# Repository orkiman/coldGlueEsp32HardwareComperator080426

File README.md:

# Cold Glue Controller — Main Controller Firmware (Stage 1)

ESP32-S3-WROOM-1-N16R8 firmware for a 4-channel high-speed cold-glue gun
controller. Up to 330 Hz droplet rate; current chopping is handled by the
on-board LM339 hardware loop. The ESP32 only orchestrates phase transitions.

See `docs/initial prompt.md` for the full hardware architecture and operational
spec.

## Toolchain

PlatformIO (recommended). Open the project folder in VS Code with the
PlatformIO extension and use `PlatformIO: Upload` / `Monitor`.

```
pio run -t upload
pio device monitor
```

## Source Tree

```
src/
  main.cpp                          task wiring + boot order
  config/Config.{h,cpp}             double-buffered config + pattern storage
  comms/
    Events.{h,cpp}                  Core1->Core0 lock-free event queue
    UartJson.{h,cpp}                NDJSON parser + command dispatcher
  hw/
    Pins.h                          pin map (verbatim from docs)
    Driver.{h,cpp}                  IN1/IN2/MUX_SELECT abstraction, killAll
    Dac.{h,cpp}                     MCP4728 with task-serialized I2C writes
    Encoder.{h,cpp}                 PCNT counter + photocell ISR (any-edge)
  rt/
    GunSequencer.{h,cpp}            per-gun Peak/Hold/Decay state machine
    PatternScheduler.{h,cpp}        sheet FIFO + lazy pattern walker
    Control.{h,cpp}                 surface called by JSON dispatcher
  sys/
    Fault.{h,cpp}                   nFAULT ISR -> master kill
    Watchdog.{h,cpp}                HMI link timeout
    Status.{h,cpp}                  5 Hz status emitter
```

## Task Layout

| Core | Task        | Prio | Purpose                                |
| ---- | ----------- | ---- | -------------------------------------- |
| 0    | `uart_rx`   | 4    | NDJSON parser                          |
| 0    | `evt_emit`  | 5    | Drains event queue to Serial           |
| 0    | `wdog`      | 3    | HMI link watchdog                      |
| 0    | `status`    | 2    | 5 Hz `{"event":"status"}`              |
| 1    | `pattern`   | 7    | Encoder poll + fire pattern events     |
| 1    | `dac`       | 6    | Coalesced MCP4728 I2C writes           |
| 1    | ISRs        | IRAM | Peak (x4), photocell, nFAULT, PCNT     |

## Protocol

Newline-delimited JSON over UART0 (115200 8N1) on GPIO 43 TX / GPIO 44 RX,
routed through the on-board CP2102 USB-UART for development.

Commands and events follow `docs/initial prompt.md` Section 8 exactly.

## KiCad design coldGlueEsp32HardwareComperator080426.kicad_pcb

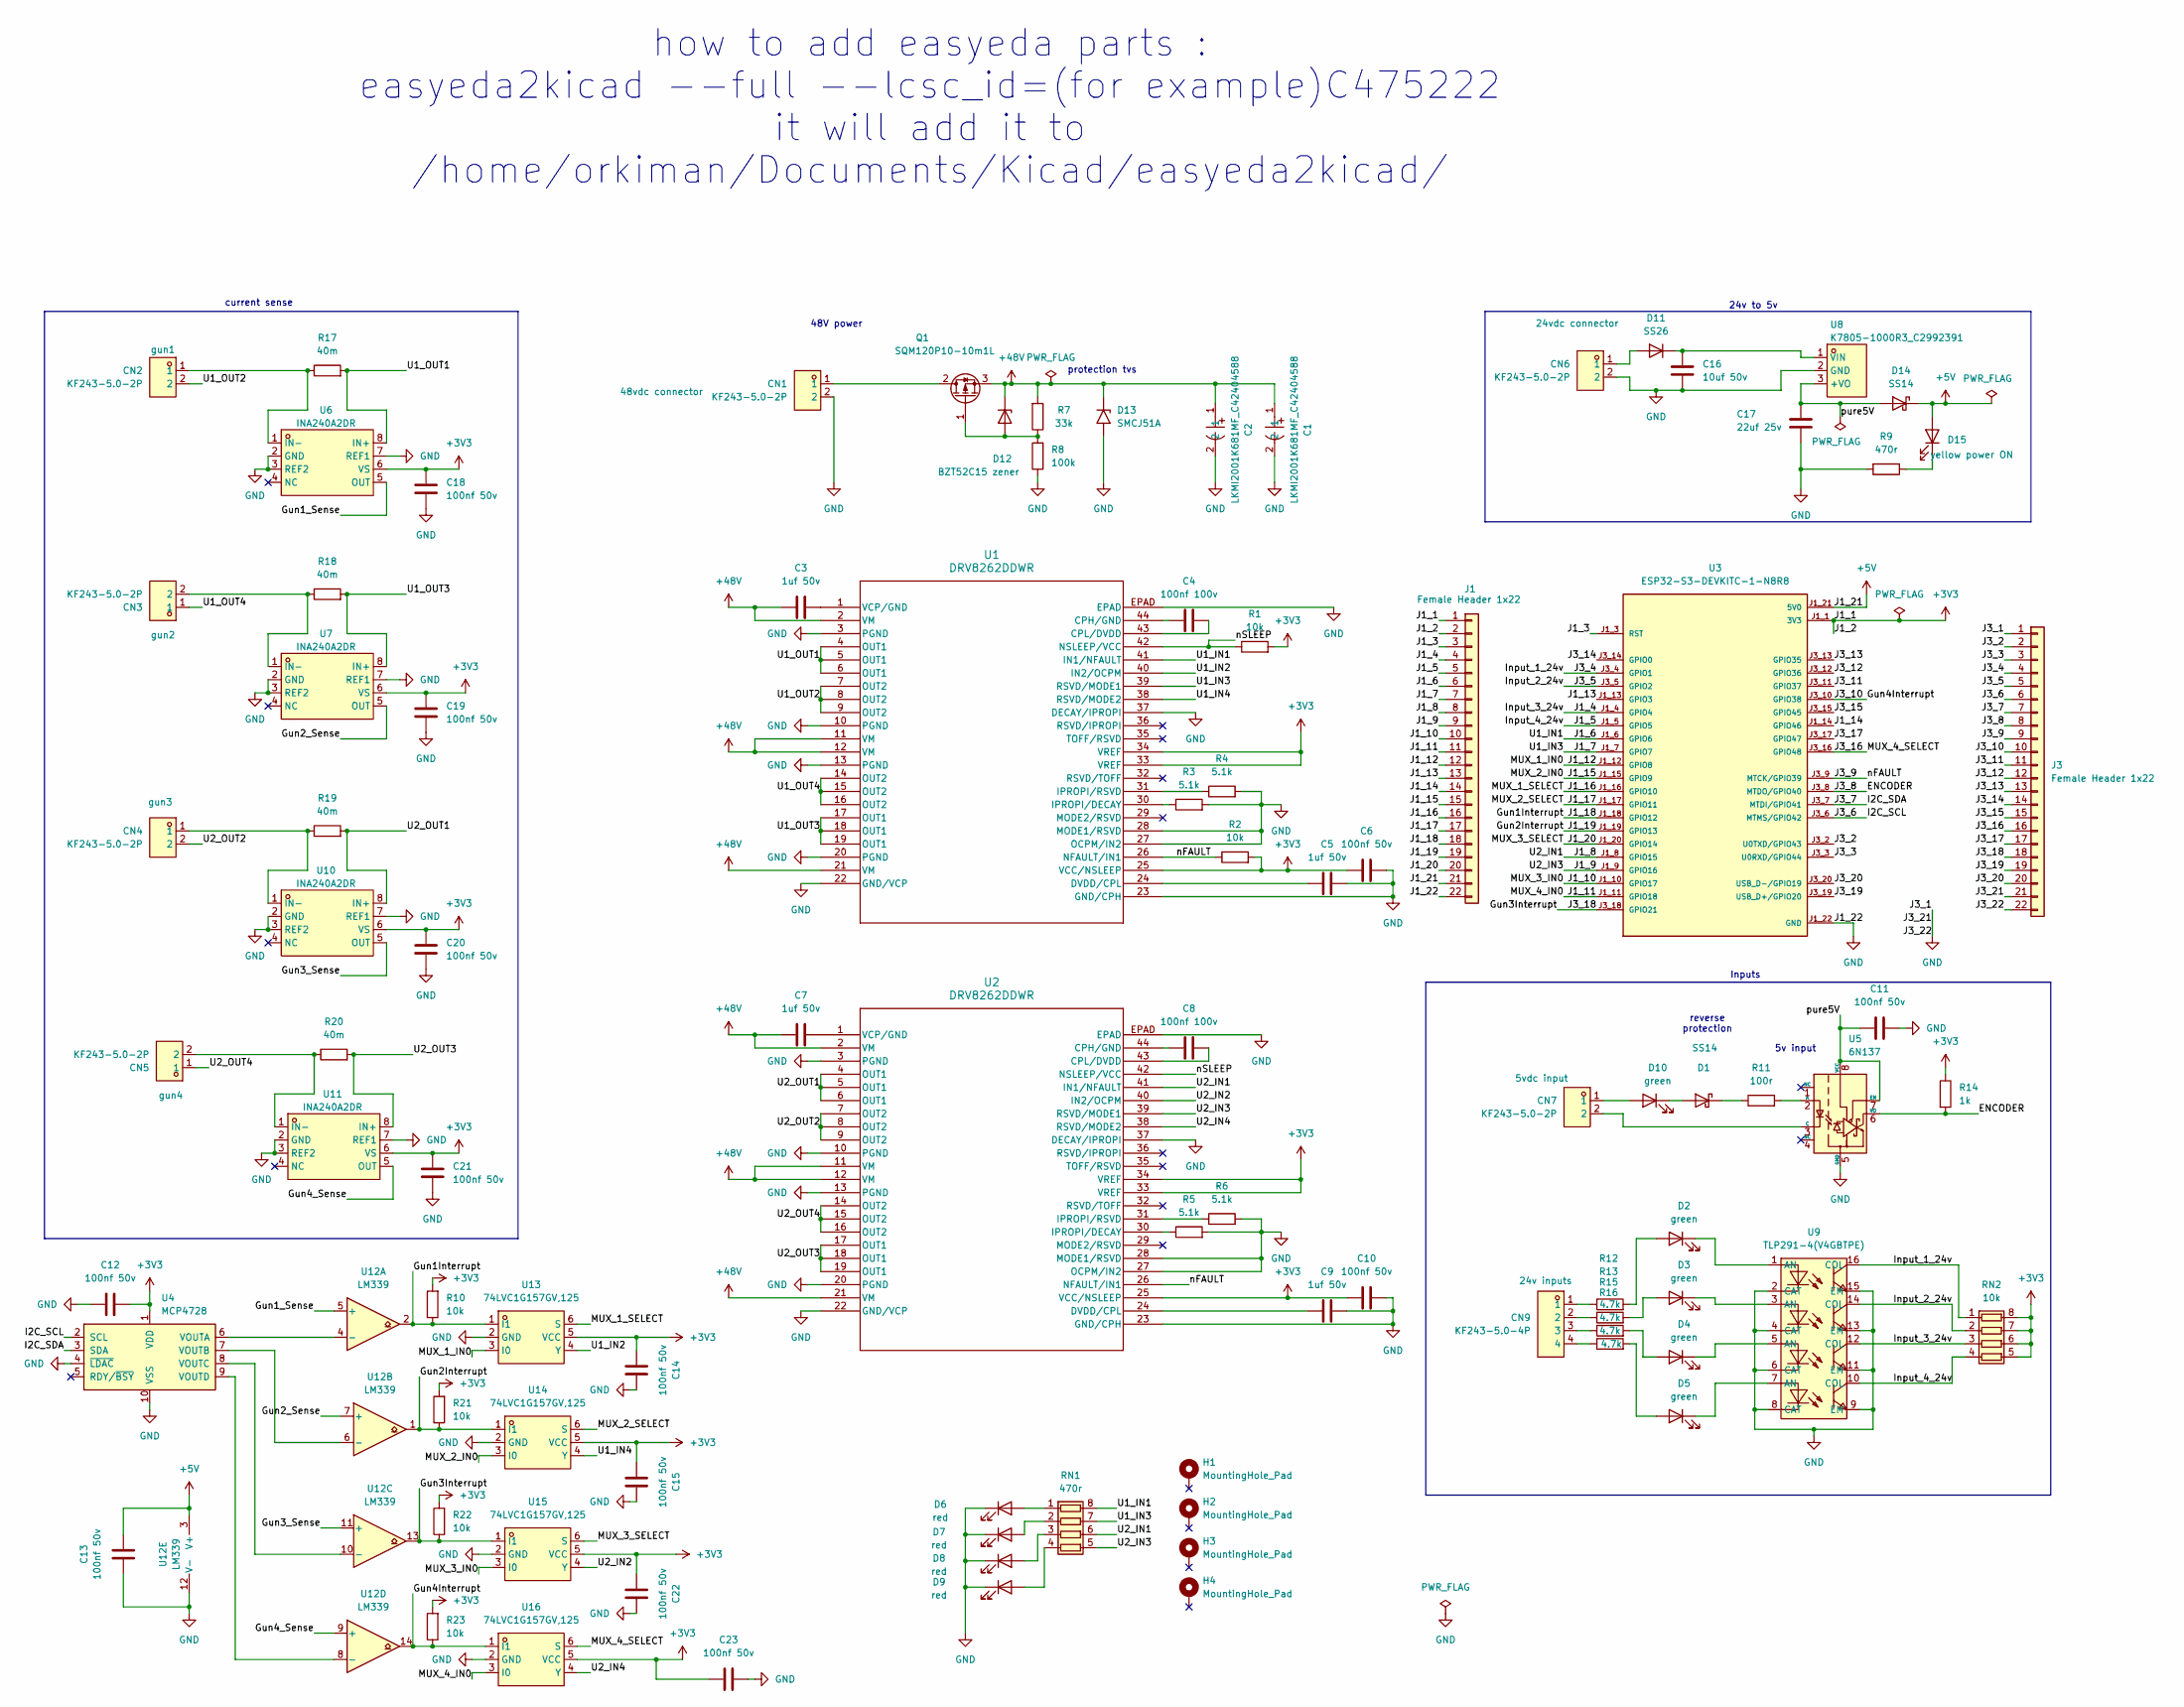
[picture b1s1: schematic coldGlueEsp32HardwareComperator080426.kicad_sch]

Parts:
C1, C2: LKMI2001K681MF_C42404588; CAP-TH_BD16.0-P7.50-D0.8-FD; LCSC part C42404588
C3, C5, C7, C9: 1uf 50v; C_0603_1608Metric; lcsc C106248
C4, C8: 100nf 100v; C_0805_2012Metric; lcsc C113803
C6, C10, C11, C12, C13, C14, C15, C22, C23: 100nf 50v; C_0603_1608Metric; lcsc C309458
C16: 10uf 50v; C_1206_3216Metric; lcsc C513774
C17: 22uf 25v; C_1206_3216Metric; lcsc C513771
C18, C19, C20, C21: 100nf 50v; C_0603_1608Metric; LCSC part C14663
CN1, CN2, CN3, CN4, CN5, CN6, CN7: KF243-5.0-2P; CONN-TH_P5.00_KF243-5.0-2P; LCSC part C475222
CN9: KF243-5.0-4P; CONN-TH_4P-P5.00_KF243-5.0-4P; LCSC part C475224
D1: SS14; D_SMA; part ss14; LCSC part C2480
D2, D3, D4, D5, D10: green; LED_0805_2012Metric; lcsc C2297
D6, D7, D8, D9: red; LED_0805_2012Metric; LCSC part C84256
D11: SS26; D_SMA; part ss26; LCSC part C14238
D12: BZT52C15 zener; D_SOD-123; LCSC part C2104
D13: SMCJ51A; D_SMC; LCSC part C438115
D14: SS14; D_SMA; LCSC part C2480
D15: yellow power ON; LED_0805_2012Metric; lcsc C2297
H1, H2, H3, H4: MountingHole_Pad; MountingHole_3.2mm_M3_Pad
J1, J3: Female Header 1x22; PinSocket_1x22_P2.54mm_Vertical; LCSC part C7499337
Q1: SQM120P10-10m1L; TO-263-2; LCSC part C3281565
R1, R2, R10, R21, R22, R23: 10k; R_0603_1608Metric; lcsc C84376
R3, R4, R5, R6: 5.1k; R_0603_1608Metric; LCSC part C23186
R7: 33k; R_0805_2012Metric; LCSC part C17633
R8: 100k; R_0805_2012Metric; LCSC part C25611
R9: 470r; R_0603_1608Metric; LCSC part C23179
R11: 100r; R_0603_1608Metric; LCSC part C22775
R12, R13, R15, R16: 4.7k; R_1206_3216Metric; LCSC part C17936
R14: 1k; R_0603_1608Metric; LCSC part C21190
R17, R18, R19, R20: 40m; R_2512_6332Metric; lcsc C500722
RN1: 470r; R_Array_Convex_4x0603; LCSC part C354986
RN2: 10k; R_Array_Convex_4x0603; LCSC part C107374
U1, U2: DRV8262DDWR; HTSSOP44-DDW_TEX; LCSC part C22427252
U3: ESP32-S3-DEVKITC-1-N8R8; XCVR_ESP32-S3-DEVKITC-1-N8R2; PARTREV V1
U4: MCP4728; MSOP-10_3x3mm_P0.5mm; LCSC part C478093
U5: 6N137; SMDIP-8_W9.53mm; LCSC part C16496
U6, U7, U10, U11: INA240A2DR; SOIC-8_L4.9-W3.9-P1.27-LS6.0-BL; LCSC part C2060768
U8: K7805-1000R3_C2992391; PWRM-TH_YLPTEC_K78XX-1000R3; LCSC part C2992391
U9: TLP291-4(V4GBTPE); SOP-16_L10.3-W4.4-P1.27-LS7.0-BL; LCSC part C2848503
U12: LM339; SOIC-14_3.9x8.7mm_P1.27mm; LCSC part C7948
U13, U14, U15, U16: 74LVC1G157GV,125; TSOP-6_L3.0-W1.5-P0.95-LS2.8-BR; MPN 74LVC1G157GV,125; LCSC part C503437

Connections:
+3V3: C6.1, C10.1, C12.2, C14.1, C15.1, C18.1, C19.1, C20.1, C21.1, C22.1, C23.1, J1.1, J1.2, R1.2, R2.2, R10.2, R14.1, R21.2, R22.2, R23.2, RN2.5 (R4.2), RN2.6 (R3.2), RN2.7 (R2.2), RN2.8 (R1.2), U1.25 (VCC/NSLEEP), U1.33 (VREF), U1.34 (VREF), U2.25 (VCC/NSLEEP), U2.33 (VREF), U2.34 (VREF), U3.J1_1 (3V3), U3.J1_2 (3V3), U4.1 (VDD), U6.6 (VS), U7.6 (VS), U10.6 (VS), U11.6 (VS), U13.5 (VCC), U14.5 (VCC), U15.5 (VCC), U16.5 (VCC)
+5V: C13.2, D14.1 (K), D15.2 (A), J1.21, U3.J1_21 (5V0), U12.3 (V+)
+48V: C1.1, C2.1, C3.1, C7.1, D12.1 (K), D13.1 (A1), Q1.3 (S), R7.2, U1.2 (VM), U1.11 (VM), U1.12 (VM), U1.21 (VM), U2.2 (VM), U2.11 (VM), U2.12 (VM), U2.21 (VM)
/ENCODER: J3.8, R14.2, U3.J3_8 (MTDO/GPIO40), U5.6 (VO)
/Gun1Interrupt: J1.18, R10.1, U3.J1_18 (GPIO12), U12.2, U13.1 (I1)
/Gun1_Sense: U6.5 (OUT), U12.5 (+)
/Gun2Interrupt: J1.19, R21.1, U3.J1_19 (GPIO13), U12.1, U14.1 (I1)
/Gun2_Sense: U7.5 (OUT), U12.7 (+)
/Gun3Interrupt: J3.18, R22.1, U3.J3_18 (GPIO21), U12.13, U15.1 (I1)
/Gun3_Sense: U10.5 (OUT), U12.11 (+)
/Gun4Interrupt: J3.10, R23.1, U3.J3_10 (GPIO38), U12.14, U16.1 (I1)
/Gun4_Sense: U11.5 (OUT), U12.9 (+)
/I2C_SCL: J3.6, U3.J3_6 (MTMS/GPIO42), U4.2 (SCL)
/I2C_SDA: J3.7, U3.J3_7 (MTDI/GPIO41), U4.3 (SDA)
/Input_1_24v: J3.4, RN2.1 (R1.1), U3.J3_4 (GPIO1), U9.16 (COL)
/Input_2_24v: J3.5, RN2.2 (R2.1), U3.J3_5 (GPIO2), U9.14 (COL)
/Input_3_24v: J1.4, RN2.3 (R3.1), U3.J1_4 (GPIO4), U9.12 (COL)
/Input_4_24v: J1.5, RN2.4 (R4.1), U3.J1_5 (GPIO5), U9.10 (COL)
/J1_3: J1.3, U3.J1_3 (RST)
/J1_6: J1.6, RN1.8 (R1.2), U1.41 (IN1/NFAULT), U3.J1_6 (GPIO6)
/J1_7: J1.7, RN1.7 (R2.2), U1.39 (RSVD/MODE1), U3.J1_7 (GPIO7)
/J1_8: J1.8, RN1.6 (R3.2), U2.41 (IN1/NFAULT), U3.J1_8 (GPIO15)
/J1_9: J1.9, RN1.5 (R4.2), U2.39 (RSVD/MODE1), U3.J1_9 (GPIO16)
/J1_10: J1.10, U3.J1_10 (GPIO17), U15.3 (I0)
/J1_11: J1.11, U3.J1_11 (GPIO18), U16.3 (I0)
/J1_12: J1.12, U3.J1_12 (GPIO8), U13.3 (I0)
/J1_13: J1.13, U3.J1_13 (GPIO3)
/J1_14: J1.14, U3.J1_14 (GPIO46)
/J1_15: J1.15, U3.J1_15 (GPIO9), U14.3 (I0)
/J1_16: J1.16, U3.J1_16 (GPIO10), U13.6 (S)
/J1_17: J1.17, U3.J1_17 (GPIO11), U14.6 (S)
/J1_20: J1.20, U3.J1_20 (GPIO14), U15.6 (S)
/J3_2: J3.2, U3.J3_2 (U0TXD/GPIO43)
/J3_3: J3.3, U3.J3_3 (U0RXD/GPIO44)
/J3_9: J3.9, R2.1, U1.26 (NFAULT/IN1), U2.26 (NFAULT/IN1), U3.J3_9 (MTCK/GPIO39)
/J3_11: J3.11, U3.J3_11 (GPIO37)
/J3_12: J3.12, U3.J3_12 (GPIO36)
/J3_13: J3.13, U3.J3_13 (GPIO35)
/J3_14: J3.14, U3.J3_14 (GPIO0)
/J3_15: J3.15, U3.J3_15 (GPIO45)
/J3_16: J3.16, U3.J3_16 (GPIO48), U16.6 (S)
/J3_17: J3.17, U3.J3_17 (GPIO47)
/J3_19: J3.19, U3.J3_19 (USB_D+/GPIO20)
/J3_20: J3.20, U3.J3_20 (USB_D-/GPIO19)
/U1_IN2: U1.40 (IN2/OCPM), U13.4 (Y)
/U1_IN4: U1.38 (RSVD/MODE2), U14.4 (Y)
/U1_OUT1: R17.2, U1.4 (OUT1), U1.5 (OUT1), U1.6 (OUT1), U6.8 (IN+)
/U1_OUT2: CN2.2, U1.7 (OUT2), U1.8 (OUT2), U1.9 (OUT2)
/U1_OUT3: R18.2, U1.17 (OUT1), U1.18 (OUT1), U1.19 (OUT1), U7.8 (IN+)
/U1_OUT4: CN3.1, U1.14 (OUT2), U1.15 (OUT2), U1.16 (OUT2)
/U2_IN2: U2.40 (IN2/OCPM), U15.4 (Y)
/U2_IN4: U2.38 (RSVD/MODE2), U16.4 (Y)
/U2_OUT1: R19.2, U2.4 (OUT1), U2.5 (OUT1), U2.6 (OUT1), U10.8 (IN+)
/U2_OUT2: CN4.2, U2.7 (OUT2), U2.8 (OUT2), U2.9 (OUT2)
/U2_OUT3: R20.2, U2.17 (OUT1), U2.18 (OUT1), U2.19 (OUT1), U11.8 (IN+)
/U2_OUT4: CN5.1, U2.14 (OUT2), U2.15 (OUT2), U2.16 (OUT2)
/nSLEEP: R1.1, U1.42 (NSLEEP/VCC), U2.42 (NSLEEP/VCC)
/pure5V: C11.1, C17.1, D14.2 (A), U5.7 (EN), U5.8 (VCC), U8.3 (+VO)
GND: C1.2, C2.2, C5.2, C6.2, C9.2, C10.2, C11.2, C12.1, C13.1, C14.2, C15.2, C16.2, C17.2, C18.2, C19.2, C20.2, C21.2, C22.2, C23.2, CN1.2, CN6.2, D6.1 (K), D7.1 (K), D8.1 (K), D9.1 (K), D13.2 (A2), J1.22, J3.1, J3.21, J3.22, R3.2, R4.2, R5.2, R6.2, R8.1, R9.2, U1.3 (PGND), U1.10 (PGND), U1.13 (PGND), U1.20 (PGND), U1.22 (GND/VCP), U1.23 (GND/CPH), U1.27 (OCPM/IN2), U1.28 (MODE1/RSVD), U1.37 (DECAY/IPROPI), U1.EPAD, U2.3 (PGND), U2.10 (PGND), U2.13 (PGND), U2.20 (PGND), U2.22 (GND/VCP), U2.23 (GND/CPH), U2.27 (OCPM/IN2), U2.28 (MODE1/RSVD), U2.37 (DECAY/IPROPI), U2.EPAD, U3.J1_22 (GND), U3.J3_1 (GND), U3.J3_21 (GND), U3.J3_22 (GND), U4.4 (~LDAC), U4.10 (VSS), U5.5 (GND), U6.2 (GND), U6.3 (REF2), U6.7 (REF1), U7.2 (GND), U7.3 (REF2), U7.7 (REF1), U8.2 (GND), U9.2 (CAT), U9.4 (CAT), U9.6 (CAT), U9.8 (CAT), U9.9 (EM), U9.11 (EM), U9.13 (EM), U9.15 (EM), U10.2 (GND), U10.3 (REF2), U10.7 (REF1), U11.2 (GND), U11.3 (REF2), U11.7 (REF1), U12.12 (V-), U13.2 (GND), U14.2 (GND), U15.2 (GND), U16.2 (GND)
unnamed: CN9.1, R12.1
unnamed: CN9.2, R13.1
unnamed: CN9.3, R15.1
unnamed: CN9.4, R16.1
unnamed: D1.2 (A), D10.1 (K)
unnamed: D1.1 (K), R11.1
unnamed: D2.2 (A), R12.2
unnamed: D2.1 (K), U9.1 (AN)
unnamed: D3.2 (A), R13.2
unnamed: D3.1 (K), U9.3 (AN)
unnamed: D4.2 (A), R15.2
unnamed: D4.1 (K), U9.5 (AN)
unnamed: D5.2 (A), R16.2
unnamed: D5.1 (K), U9.7 (AN)
unnamed: D6.2 (A), RN1.1 (R1.1)
unnamed: D7.2 (A), RN1.2 (R2.1)
unnamed: D8.2 (A), RN1.3 (R3.1)
unnamed: D9.2 (A), RN1.4 (R4.1)
unnamed: CN7.1, D10.2 (A)
unnamed: CN6.1, D11.2 (A)
unnamed: C16.1, D11.1 (K), U8.1 (VIN)
unnamed: D12.2 (A), Q1.1 (G), R7.1, R8.2
unnamed: D15.1 (K), R9.1
unnamed: CN1.1, Q1.2 (D)
unnamed: C4.1, U1.44 (CPH/GND)
unnamed: C4.2, U1.43 (CPL/DVDD)
unnamed: C5.1, U1.24 (DVDD/CPL)
unnamed: R3.1, U1.30 (IPROPI/DECAY)
unnamed: R4.1, U1.31 (IPROPI/RSVD)
unnamed: C3.2, U1.1 (VCP/GND)
unnamed: C8.1, U2.44 (CPH/GND)
unnamed: C8.2, U2.43 (CPL/DVDD)
unnamed: C9.1, U2.24 (DVDD/CPL)
unnamed: R5.1, U2.30 (IPROPI/DECAY)
unnamed: R6.1, U2.31 (IPROPI/RSVD)
unnamed: C7.2, U2.1 (VCP/GND)
unnamed: R11.2, U5.2 (A)
unnamed: CN7.2, U5.3 (C)
unnamed: CN2.1, R17.1, U6.1 (IN-)
unnamed: CN3.2, R18.1, U7.1 (IN-)
unnamed: CN4.1, R19.1, U10.1 (IN-)
unnamed: CN5.2, R20.1, U11.1 (IN-)
unnamed: U4.6 (VOUTA), U12.4 (-)
unnamed: U4.7 (VOUTB), U12.6 (-)
unnamed: U4.8 (VOUTC), U12.10 (-)
unnamed: U4.9 (VOUTD), U12.8 (-)

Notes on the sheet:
48V power
Inputs
reverse protection
how to add easyeda parts : easyeda2kicad --full --lcsc_id=(for example)C475222 it will add it to /home/orkiman/Documents/Kicad/easyeda2kicad/
24v to 5v
current sense
5v input
protection tvs

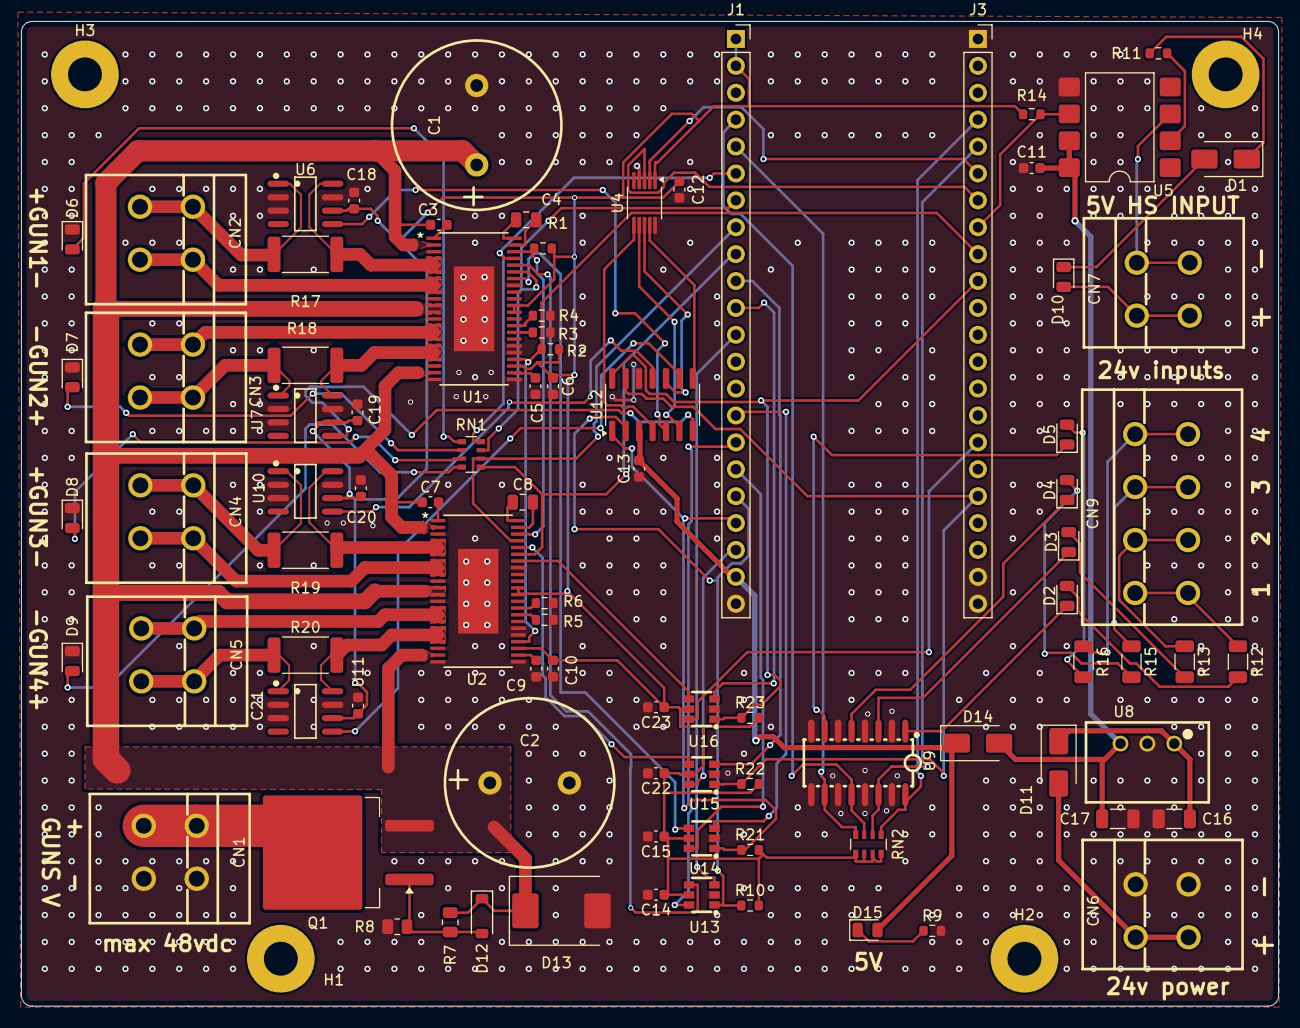
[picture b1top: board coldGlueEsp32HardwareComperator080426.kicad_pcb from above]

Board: 2 copper layers, 118.7 x 93.0 mm, 93 parts (0 on the bottom side), 92 nets.

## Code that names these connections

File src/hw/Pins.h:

#pragma once
#include <stdint.h>

// =============================================================================
// Cold Glue Controller - ESP32-S3 Pin Map
// Source of truth: docs/initial prompt.md  Section 4
// =============================================================================

namespace pins {

constexpr uint8_t NUM_GUNS = 4;

// Per-gun pin arrays, indexed 0..3 (Gun 1..Gun 4).
constexpr int8_t OPTO_IN[NUM_GUNS]    = { 1,  2,  4,  5  }; // 24V opto inputs (Gun1 = photocell)
constexpr int8_t DRV_IN1[NUM_GUNS]    = { 6,  7, 15, 16  }; // DRV8262 IN1/IN3 main drive
constexpr int8_t MUX_IN2[NUM_GUNS]    = { 8,  9, 17, 18  }; // MUX I0 input (manual ESP32 override)
constexpr int8_t MUX_SELECT[NUM_GUNS] = {10, 11, 14, 48  }; // S=1 LM339 control, S=0 ESP32 control
constexpr int8_t PEAK_IRQ[NUM_GUNS]   = {12, 13, 21, 38  }; // From LM339, ext 10k pull-up

// Photocell trigger is Opto Input #1 by spec ("e.g. Input_1_24v").
constexpr int8_t PHOTOCELL = OPTO_IN[0];

// --- Global pins ---
constexpr int8_t I2C_SDA  = 41;   // -> MCP4728
constexpr int8_t I2C_SCL  = 42;   // -> MCP4728
constexpr int8_t N_FAULT  = 39;   // DRV8262 nFAULT, active LOW, ext 10k pull-up
constexpr int8_t ENCODER  = 40;   // 6N137 single-channel pulse input

// --- UART0 (HMI link via CP2102 / pin header) ---
// Default Arduino Serial uses these on ESP32-S3 DevKitC-1.
constexpr int8_t UART_TX  = 43;
constexpr int8_t UART_RX  = 44;

} // namespace pins

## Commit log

2026-04-08 Initial commit: Forked to new hardware-assist design
2026-04-09 complete adding hardware comerator to schematics
2026-04-12 wiring headers and remove esp from board before routing
2026-04-13 CN3,5 fix orientation(before freerouting)
2026-04-14 complete routing
2026-04-18 routed no errors
2026-04-19 all lcsc part numbers collected
2026-04-21 thickened some 48 traces so i can use 1oz copper thickness safely
2026-04-21 lcsc collumn renamed all parts in stock now
2026-05-10 Clean up: Move remaining KiCad files and libraries to hardware directory
2026-05-10 added initial prompt file
2026-05-19 Stage 1: Complete main controller firmware scaffold
    - PlatformIO project for ESP32-S3-WROOM-1-N16R8 (16MB Flash / 8MB PSRAM)
    - Dual-core FreeRTOS architecture:
    - Core 1: Real-time pattern scheduler, gun sequencers, ISRs
    - Core 0: NDJSON UART comms, watchdog, status emitter
    - Hardware abstraction: DRV8262 driver, MCP4728 DAC (queued I2C), PCNT encoder
    - Per-gun dot sequence: Peak current → hardware-chopped Hold → Active Fast Decay
2026-05-19 docs: record Stage 2 GUI progress and per-gun on_timeout_ms landing
    - Stage 2 status updated to "In progress" — PySide6 GUI scaffold in gui/
    tree; mock-link works, real serial path implemented.
    - Per-gun `on_timeout_ms` replaces global `hold_time_ms`:
    - Moved from RuntimeConfig to GunPattern; semantics changed from
    "Hold-phase duration started by peakIsr" to "total Peak+Hold budget
    started by fire()".
